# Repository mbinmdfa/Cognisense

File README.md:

# Cognisense
Current sensor PCB for Cognisense

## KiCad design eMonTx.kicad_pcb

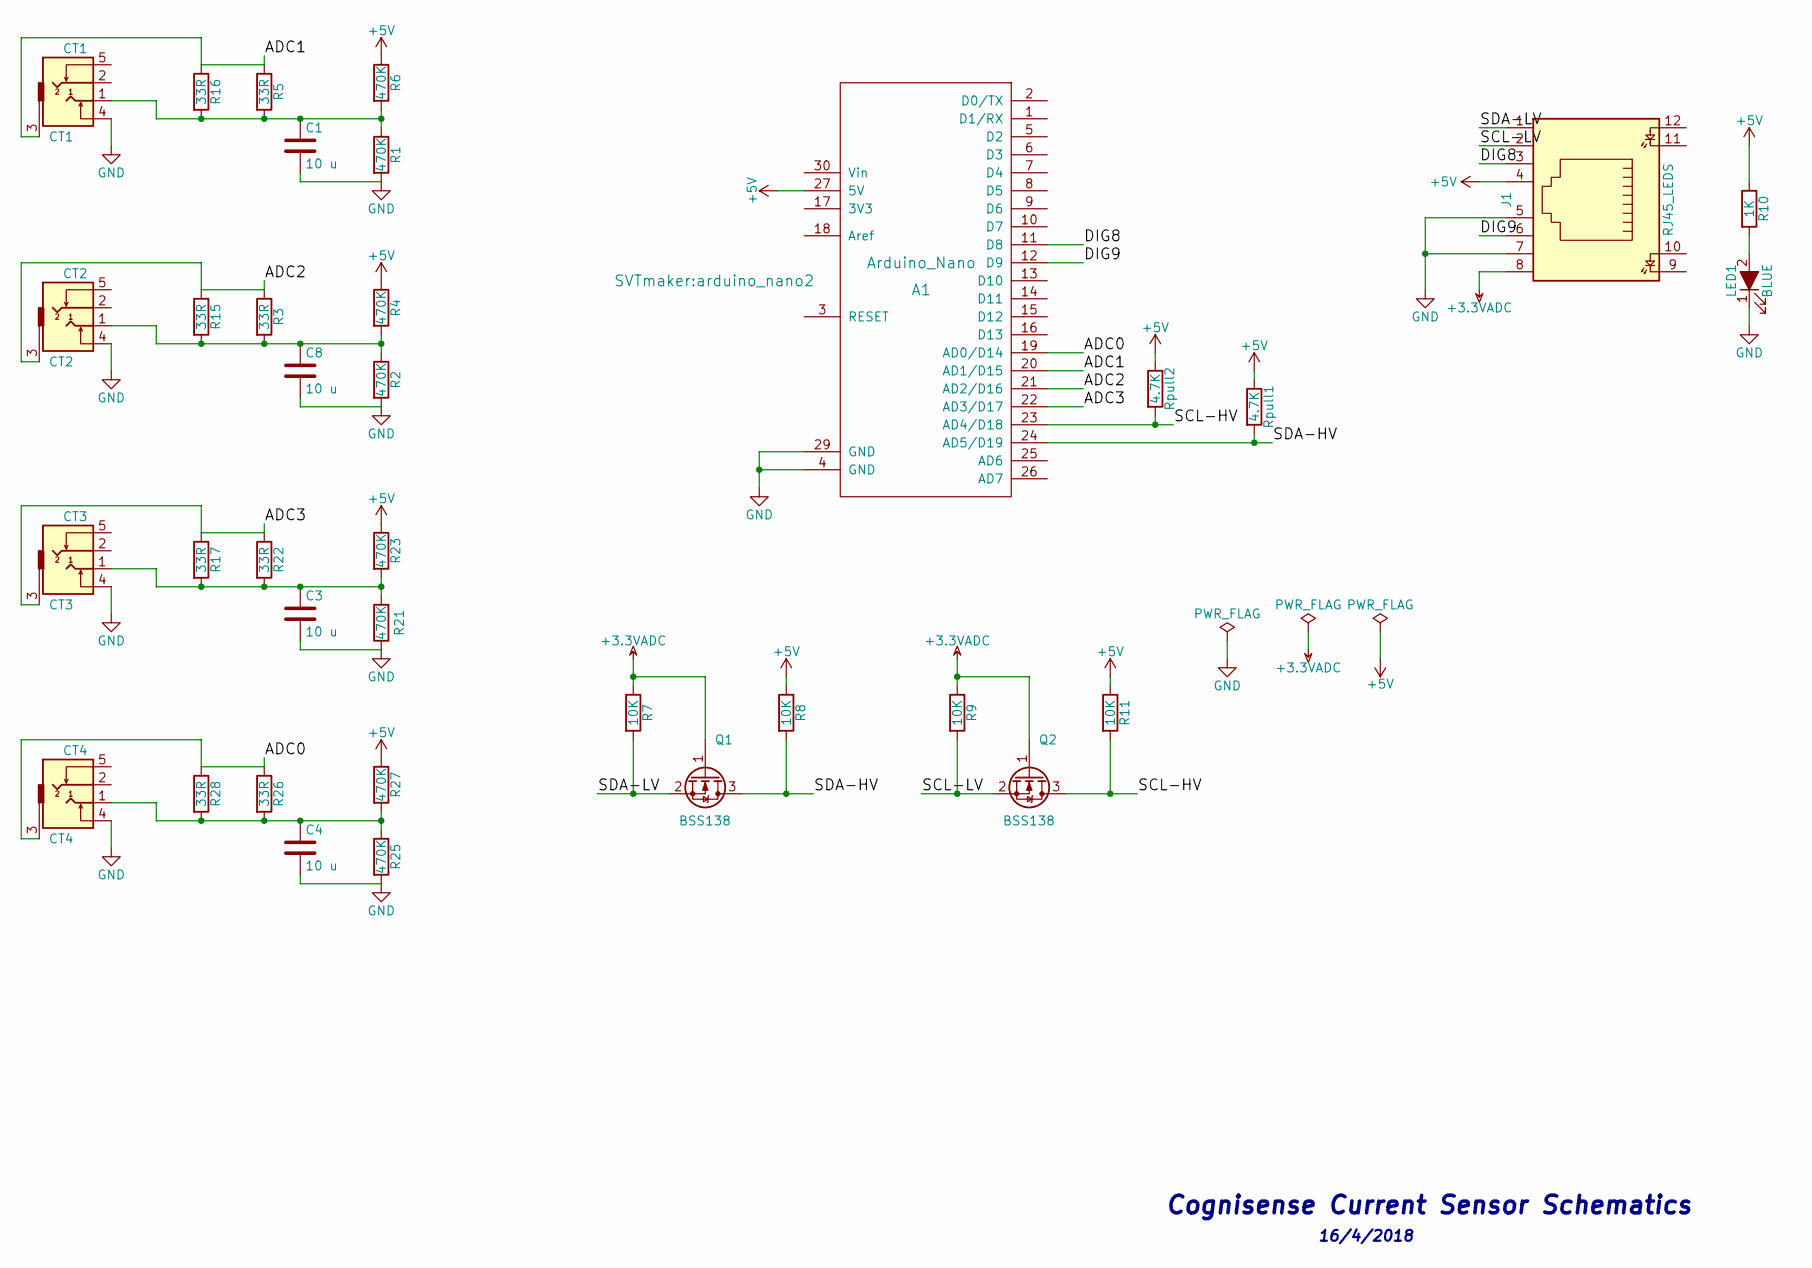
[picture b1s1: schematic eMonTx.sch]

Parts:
A1: Arduino_Nano; arduino_nano2
C1, C3, C4, C8: 10 u; C_0805_HandSoldering
CT1: CT1; Audio-LR-3.5mm
CT2: CT2; Audio-LR-3.5mm
CT3: CT3; Audio-LR-3.5mm
CT4: CT4; Audio-LR-3.5mm
J1: RJ45_LEDS; CONNECTOR_RJ45_RA_TH_LEDS
LED1: BLUE; LED_1206_HandSoldering
Q1, Q2: BSS138; SOT-23_Handsoldering
R1, R2, R4, R6, R21, R23, R25, R27: 470K; R_1206_HandSoldering
R3, R5, R15, R16, R17, R22, R26, R28: 33R; R_1206_HandSoldering
R7, R8, R9, R11: 10K; R_1206_HandSoldering
R10: 1K; R_1206_HandSoldering
Rpull1, Rpull2: 4.7K; R_1206_HandSoldering

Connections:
+3.3VADC: J1.8, Q1.1 (G), Q2.1 (G), R7.1, R9.1; also elsewhere on the board
+5V: A1.27 (5V), J1.4, R4.1, R6.1, R8.1, R10.1, R11.1, R23.1, R27.1, Rpull1.1, Rpull2.1; also elsewhere on the board
/ADC0: A1.19 (AD0/D14), CT4.3, R26.1, R28.1
/ADC1: A1.20 (AD1/D15), CT1.3, R5.1, R16.1
/ADC2: A1.21 (AD2/D16), CT2.3, R3.1, R15.1
/ADC3: A1.22 (AD3/D17), CT3.3, R17.1, R22.1
/DIG8: A1.11 (D8), J1.3
/DIG9: A1.12 (D9), J1.6
/SCL-HV: A1.23 (AD4/D18), Q2.3 (D), R11.2, Rpull2.2
/SCL-LV: J1.2, Q2.2 (S), R9.2
/SDA-HV: A1.24 (AD5/D19), Q1.3 (D), R8.2, Rpull1.2
/SDA-LV: J1.1, Q1.2 (S), R7.2
GND: A1.4 (GND), A1.29 (GND), C1.2, C3.2, C4.2, C8.2, CT1.4, CT2.4, CT3.4, CT4.4, J1.5, J1.7, LED1.1 (K), R1.2, R2.2, R21.1, R25.2
unnamed: C1.1, CT1.1, R1.1, R5.2, R6.2, R16.2
unnamed: C3.1, CT3.1, R17.2, R21.2, R22.2, R23.2
unnamed: C4.1, CT4.1, R25.1, R26.2, R27.2, R28.2
unnamed: C8.1, CT2.1, R2.1, R3.2, R4.2, R15.2
unnamed: LED1.2 (A), R10.2

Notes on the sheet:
Cognisense Current Sensor Schematics
16/4/2018

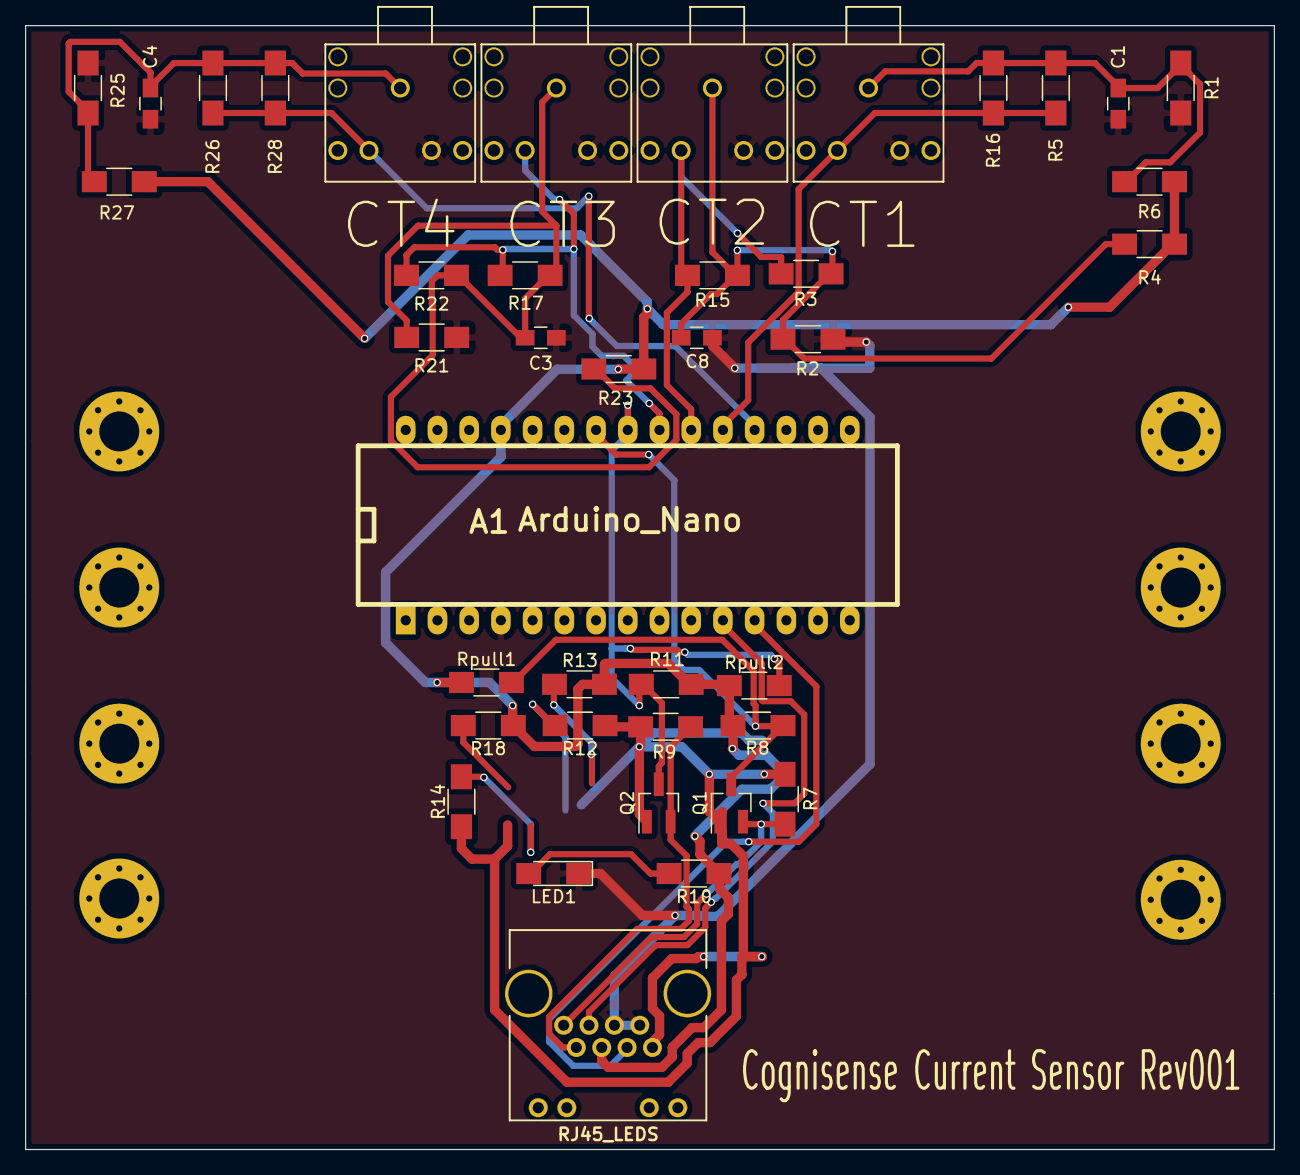
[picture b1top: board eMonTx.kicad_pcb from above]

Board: 2 copper layers, 100.0 x 90.0 mm, 40 parts (0 on the bottom side), 18 nets.

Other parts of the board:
R12, R13, R14, R18: 10K; R_1206_HandSoldering

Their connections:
+3.3VADC: R12.1, R14.1; also elsewhere on the board
+5V: R13.1, R18.1; also elsewhere on the board
